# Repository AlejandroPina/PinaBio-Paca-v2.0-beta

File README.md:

# PinaBio Paca v2.0 beta

[English](README.en.md)

Placa experimental para registrar ECG, pulso óptico (PPG), respuesta galvánica de la piel (GSR), dos bandas de respiración y temperatura, y transmitir los datos por BLE. El uso previsto es investigación y biofeedback; no es un dispositivo médico.

La nueva placa **PINABio "Paca" v.2.0.** se encuentra en [hardware/PinaBio-Paca-v2.0](hardware/PinaBio-Paca-v2.0/README.md). Es un proyecto editable de **KiCad 9.0.9**, con esquemático, PCB de cuatro capas, BOM, Gerbers, taladros y posiciones. Mide **84,50 × 53,11 mm**. KiCad 9.0.9 informa **ERC 0, DRC 0, 0 conexiones pendientes y 0 diferencias entre esquemático y PCB**. Los archivos de fabricación son una salida de prototipo; falta la inspección independiente de huellas y la validación eléctrica de la primera placa ensamblada.

## Qué lleva

- ESP32-S3-MINI-1U-N8 con antena externa U.FL, BLE y Wi-Fi desactivado.
- Dos ADS122C04: uno dedicado al ECG a 600 SPS y otro para GSR, respiración torácica, respiración abdominal y AUX.
- MCP6004, módulo AD8232 externo, módulo GY-MAX30102 externo y módulo CJMCU-30205 externo.
- LiPo protegida de una celda, BQ24074 con power-path, TPS63070 para 3V3_SYS y TLV75530PDBVR a 3,0 V solo para la temperatura.
- Un USB-C soldado en el borde para carga, programación y datos. El interruptor exterior DPDT ON-ON controla el modo del BQ24074 y la habilitación del TPS63070. Con ON y USB, el sistema funciona desde la batería y no carga.
- No hay cortes automáticos en los sensores ni aislamiento USB en la placa. Para adquirir con una persona conectada y USB presente se requiere un aislador USB externo apto para ese uso.

## Documentación

- [Proyecto y conexiones de la PCB](hardware/PinaBio-Paca-v2.0/README.md)
- [Especificación de hardware](docs/es/especificacion.md)
- [Alimentación y USB](docs/es/alimentacion-usb.md)
- [Protocolo y datos](docs/es/protocolo.md)
- [Comparación con V1](docs/es/comparacion-v1.md)

**Antes de encargar montaje:** confirmar orientación y dimensiones del USB-C, TPS63070, todos los conectores y el interruptor cableado; medir los tres módulos externos reales; verificar las transiciones ON/OFF/USB y las tensiones del cargador y reguladores. Los informes de KiCad no sustituyen estas pruebas.

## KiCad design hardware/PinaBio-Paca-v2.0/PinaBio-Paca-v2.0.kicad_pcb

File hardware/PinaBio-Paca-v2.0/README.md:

# PINABio "Paca" v.2.0.

[English](README.en.md) · [Especificación completa](../../docs/es/especificacion.md) · [Alimentación y USB](../../docs/es/alimentacion-usb.md)

Proyecto editable de **KiCad 9.0.9**, cuatro capas, **84,50 × 53,11 mm**. Implementa la arquitectura cerrada del proyecto: un USB-C soldado, BQ24074 en standby mediante interruptor exterior, sin MOSFET de corte de VBUS, dos reguladores, sin cortes automáticos de sensores ni pull-ups nuevos de I²C, dos masas unidas solo en NT1 y keepout de cobre en todas las capas bajo el extremo U.FL del ESP32. La zona del TPS63070 y la bobina mantiene los nodos SW_L1 y SW_L2 en F.Cu, 0,40 mm y sin vías; la huella RNM conserva el pin 1 arriba a la izquierda y la numeración antihoraria.

## Archivos y verificación

- `PinaBio-Paca-v2.0.kicad_sch`, `.kicad_pcb` y `.kicad_pro`: esquemático y PCB.
- `PinaBio.kicad_sym`, `lib.pretty/`, `sym-lib-table` y `fp-lib-table`: bibliotecas necesarias.
- `bom.csv`: lista de materiales con MPN. L1 es **Coilcraft XAL4020-152MEC**.
- `fab/`: Gerbers de las cuatro capas, máscaras, pasta, serigrafía, contorno, taladros PTH/NPTH y `position.csv` en milímetros. `PinaBio-Paca-v2.0-Gerbers.zip` agrupa los 14 archivos de placa y taladro para subirlos al fabricante; BOM y posiciones se entregan por separado.
- `final-erc.txt` y `final-parity.txt`: **ERC 0, DRC 0, 0 sin conectar y paridad esquema-PCB 0**, ejecutados con KiCad 9.0.9.
- `Logo PINA-reducido.jfif`: imagen fuente del logo que se convirtió a serigrafía monocroma.

Los Gerbers son **de prototipo**. Antes de fabricar o montar, otra persona debe cotejar las huellas con los componentes comprados y ensayar una primera unidad, en especial la orientación del USB-C y TPS63070, las transiciones ON/OFF/USB y el cableado de los módulos externos.

## Conectores

| Referencia | Conexión por orden de pin |
|---|---|
| J1 | USB-C HCTL HC-TYPE-C-16P-01A, boca en el borde inferior; D+ y D− pasan por USBLC6-2SC6 y resistencias de 22 Ω. |
| J2 BATT | 1 BAT+ protegido, 2 GND, 3 TS/NTC. JST PH de 3 pines. La serigrafía usa «BATT» debajo del conector. |
| J3 ECG | 1 AGND, 2 3V3_A, 3 ECG_OUT, 4 LO_N, 5 LO_P, 6 3V3_A (SDN permanentemente habilitado). Orden del módulo rojo: GND, 3.3V, OUTPUT, LO−, LO+, SDN. |
| J4 PPG | 1 3V3_SYS/VIN, 2 GND, 3 SCL, 4 SDA, 5 INT. «VIN» identifica la alimentación del módulo; las otras cuatro señales están rotuladas junto a sus pines. |
| J5 TEMP | 1 3V0_TEMP, 2 GND, 3 SDA, 4 SCL. JST PH de 4 pines; unir A0/A1/A2 a GND en el módulo CJMCU-30205. |
| J6 GSR | 1 señal GSR, 2 AGND. |
| J7 RESP T | 1 señal torácica, 2 AGND. |
| J8 RESP A | 1 señal abdominal, 2 AGND. |
| J9 BATT METER | 1 BAT+ conmutado por Q4 BSS84/Q5 BSS138, 2 GND. JST PH B2B-PH-K-S(LF)(SN), reservado para el medidor de batería. |

J9 solo entrega tensión cuando está activo **3V3_SYS** (ON con batería u OFF con USB). Q4 tiene una resistencia de 1 MΩ entre puerta y fuente. La alimentación del medidor procede de BAT_PROT y no está destinada a alimentar otros módulos.

## Interruptor y alimentación

SW1 son **seis taladros para cable**, no una huella para soldar el interruptor. La pieza de referencia en la caja es C&K **7201SYZQE**, DPDT ON-ON. Puede emplearse otro DPDT ON-ON de seis terminales, como un MTS-202, después de verificar con multímetro sus comunes y contactos. Taladros 1–6 corresponden a terminales 1–6 de la referencia C&K: 1 VLOG, 2 EN2_CE, 3 GND, 4 BAT_PROT, 5 TPS_EN y 6 VLOG.

R39 de **10 kΩ, 1 %**, junto al pin EN del TPS63070, separa TPS_EN de TPS_EN_IC. R12 de 100 kΩ queda al lado del interruptor. PS/SYNC va a masa para PWM forzado. El TLV75530PDBVR alimenta **solo** el módulo de temperatura a 3,0 V; R3 de VBUS continúa en **0 Ω**.

Con OFF y USB se carga la batería y la placa puede programarse. Con ON y USB el BQ24074 está en standby: el sistema se alimenta de la LiPo, USB lleva datos y la batería no carga. Para conectar a una persona en ese modo se exige un aislador USB externo apropiado. No hay aislador ni desconexión automática de sensores en la PCB.

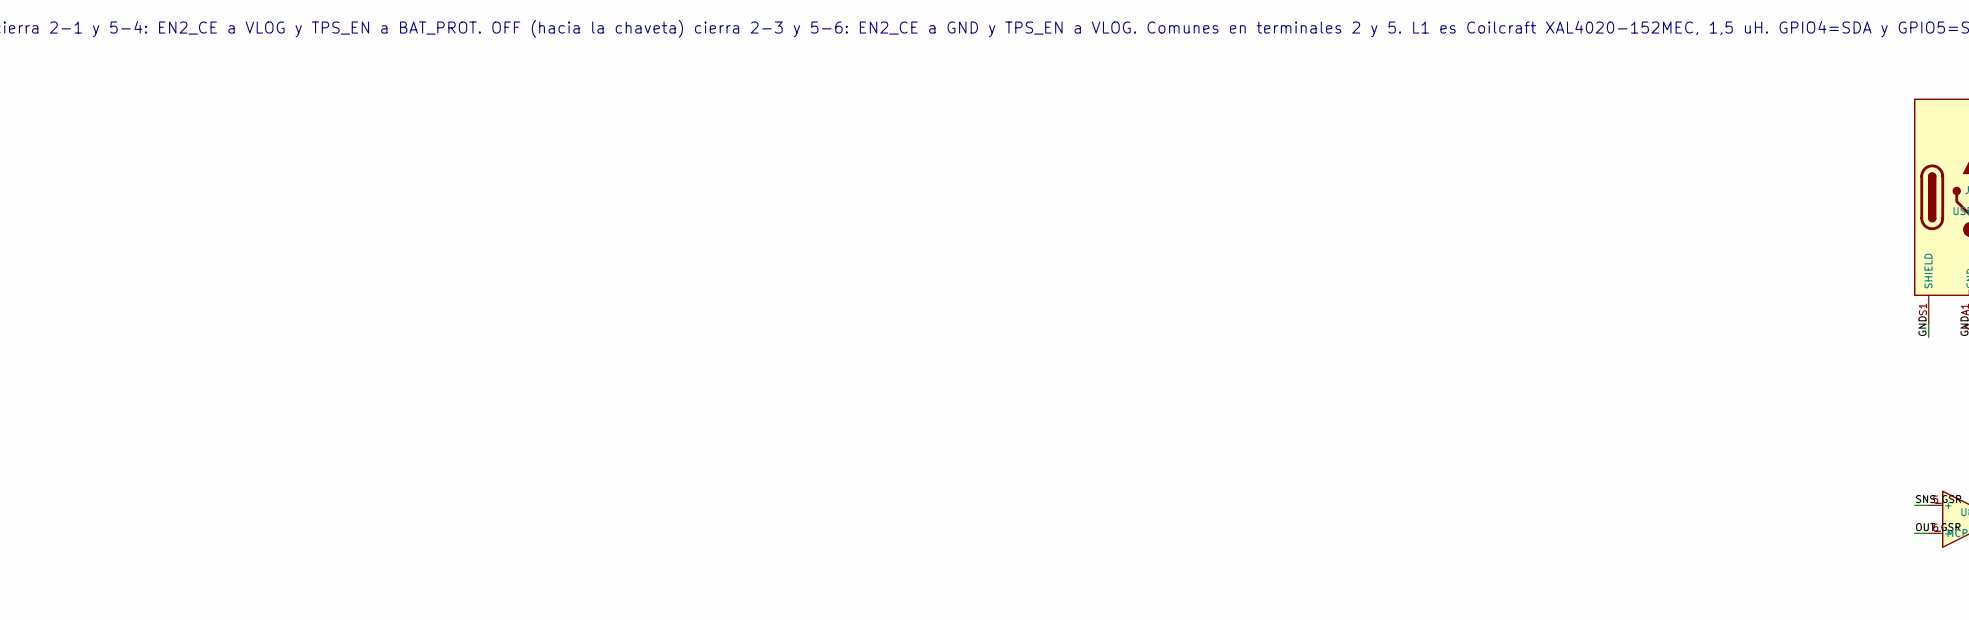
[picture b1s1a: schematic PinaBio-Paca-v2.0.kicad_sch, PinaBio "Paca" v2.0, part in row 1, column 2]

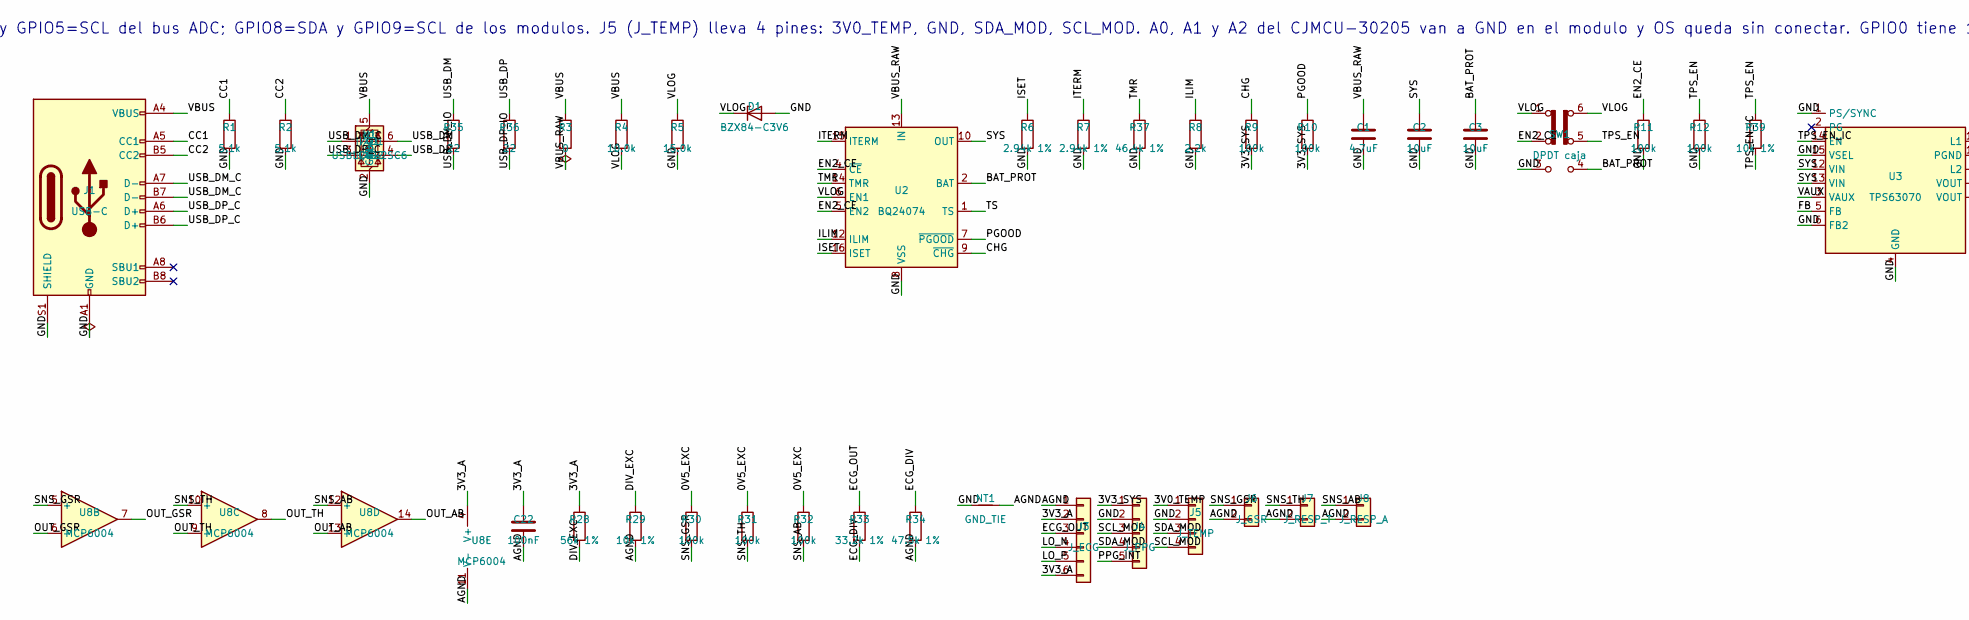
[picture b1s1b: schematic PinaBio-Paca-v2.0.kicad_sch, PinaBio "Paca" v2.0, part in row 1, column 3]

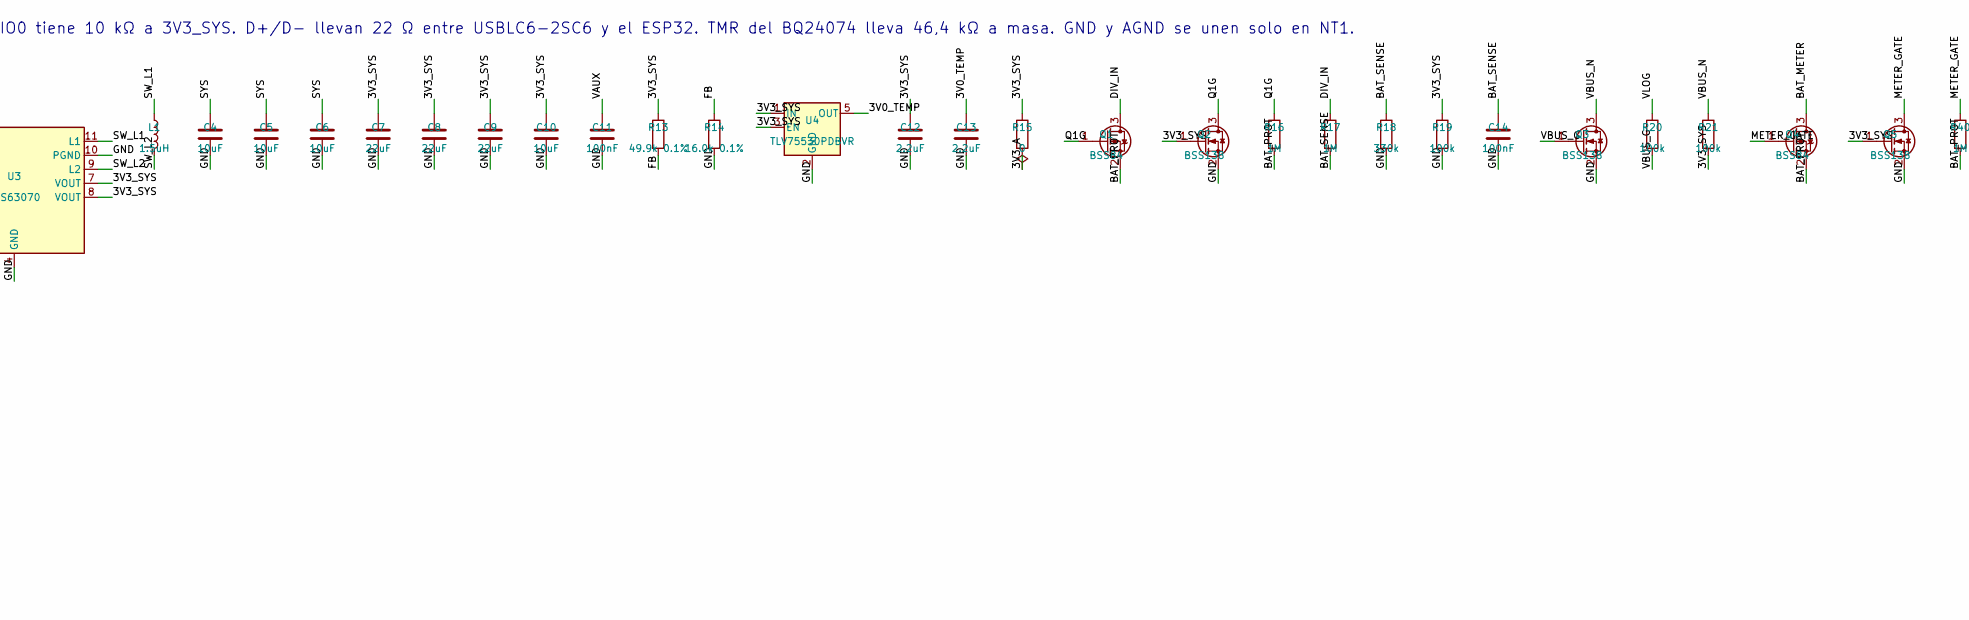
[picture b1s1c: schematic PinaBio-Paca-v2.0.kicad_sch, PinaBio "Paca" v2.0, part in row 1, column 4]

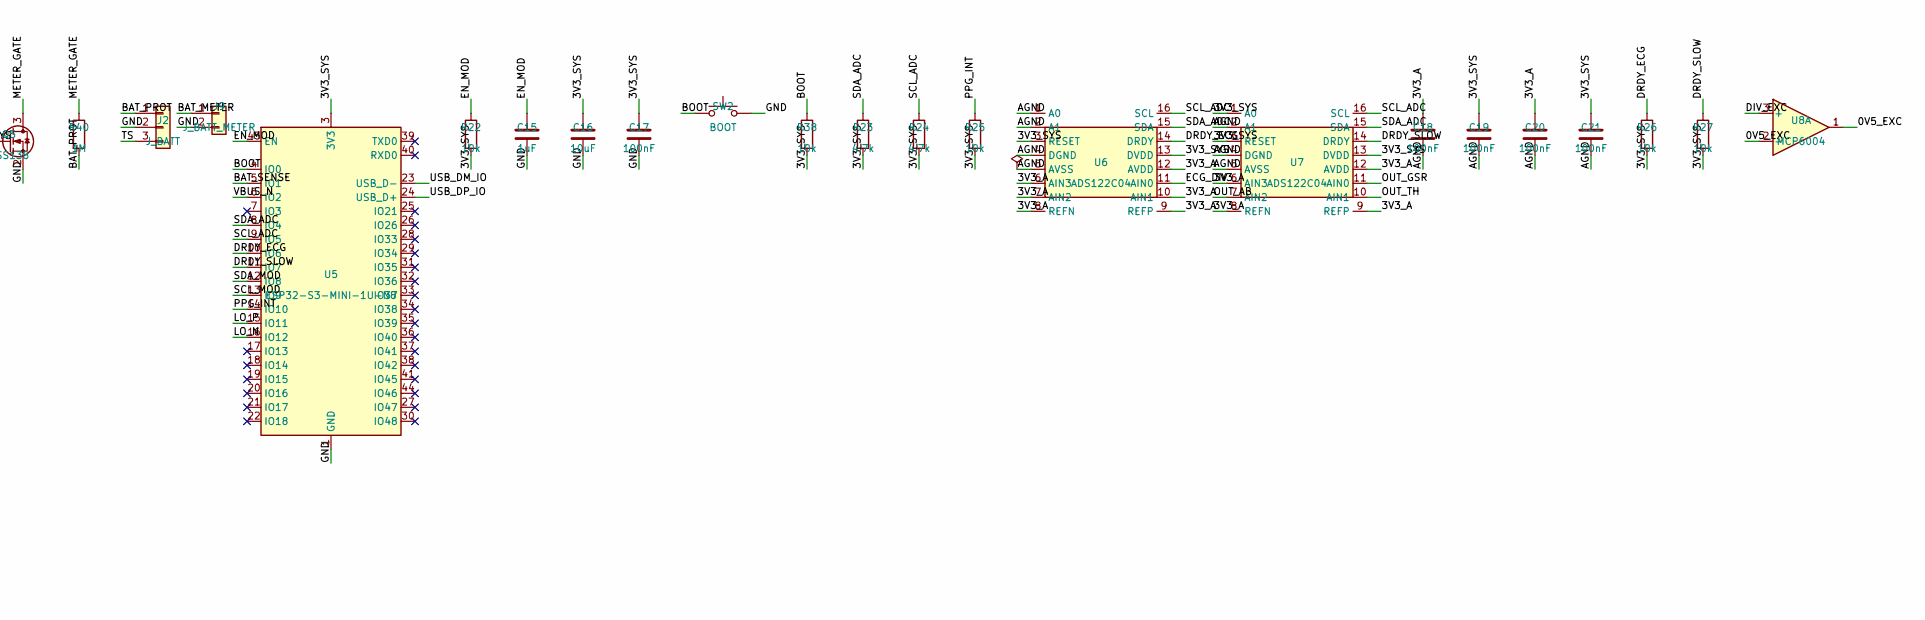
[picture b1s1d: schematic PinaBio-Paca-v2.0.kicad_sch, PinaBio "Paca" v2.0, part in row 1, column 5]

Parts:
C1: 4.7uF; C_0603_1608Metric; Voltage 16V; MPN CL10A475KO8NNNC
C2, C3, C4, C5, C6, C10, C16: 10uF; C_0805_2012Metric; Voltage 16V; MPN CL21A106KOQNNNE
C7, C8, C9: 22uF; C_0805_2012Metric; Voltage 25V; MPN CL21A226MAYNNNE
C11, C14, C17, C18, C19, C20, C21, C22: 100nF; C_0603_1608Metric; Voltage 50V; MPN CL10B104KB8NNNC
C12, C13: 2.2uF; C_0805_2012Metric; Voltage 25V; MPN CL21B225KAFNNNE
C15: 1uF; C_0603_1608Metric; Voltage 50V; MPN CL10A105KB8NNNC
D1: BZX84-C3V6; SOT-23; MPN BZX84-C3V6,215
J1: USB-C; USB_C_Receptacle_HCTL_HC-TYPE-C-16P-01A; MPN HC-TYPE-C-16P-01A
J2: J_BATT; JST_PH_B3B-PH-K_1x03_P2.00mm_Vertical; MPN B3B-PH-K-S(LF)(SN)
J3: J_ECG; JST_PH_B6B-PH-K_1x06_P2.00mm_Vertical; MPN B6B-PH-K-S(LF)(SN)
J4: J_PPG; JST_PH_B5B-PH-K_1x05_P2.00mm_Vertical; MPN B5B-PH-K-S(LF)(SN)
J5: J_TEMP; JST_PH_B4B-PH-K_1x04_P2.00mm_Vertical; MPN B4B-PH-K-S(LF)(SN)
J6: J_GSR; JST_PH_B2B-PH-K_1x02_P2.00mm_Vertical; MPN B2B-PH-K-S(LF)(SN)
J7: J_RESP_T; JST_PH_B2B-PH-K_1x02_P2.00mm_Vertical; MPN B2B-PH-K-S(LF)(SN)
J8: J_RESP_A; JST_PH_B2B-PH-K_1x02_P2.00mm_Vertical; MPN B2B-PH-K-S(LF)(SN)
J9: J_BATT_METER; JST_PH_B2B-PH-K_1x02_P2.00mm_Vertical; MPN B2B-PH-K-S(LF)(SN)
L1: 1.5uH; L_Coilcraft_XAL4020-XXX; MPN XAL4020-152MEC
NT1: GND_TIE; GndTie_2mm
Q1, Q4: BSS84; SOT-23; MPN BSS84LT1G
Q2, Q3, Q5: BSS138; SOT-23; MPN BSS138LT1G
R1, R2: 5.1k; R_0603_1608Metric; MPN RC0603FR-075K1L
R3, R15: 0; R_0603_1608Metric; MPN RC0603JR-070RL
R4: 10.0k; R_0603_1608Metric; MPN RC0603FR-0710KL
R5: 15.0k; R_0603_1608Metric; MPN RC0603FR-0715KL
R6, R7: 2.94k 1%; R_0603_1608Metric; MPN RC0603FR-072K94L
R8: 2.2k; R_0603_1608Metric; MPN RC0603FR-072K2L
R9, R10, R11, R12, R19, R20, R21, R30, R31, R32: 100k; R_0603_1608Metric; MPN RC0603FR-07100KL
R13: 49.9k 0.1%; R_0603_1608Metric; MPN RT0603BRD0749K9L
R14: 16.0k 0.1%; R_0603_1608Metric; MPN RT0603BRD0716KL
R16, R17, R40: 1M; R_0603_1608Metric; MPN RC0603FR-071ML
R18: 330k; R_0603_1608Metric; MPN RC0603FR-07330KL
R22, R25, R26, R27, R38: 10k; R_0603_1608Metric; MPN RC0603FR-0710KL
R23, R24: 4.7k; R_0603_1608Metric; MPN RC0603FR-074K7L
R28: 56k 1%; R_0603_1608Metric; MPN RC0603FR-0756KL
R29, R39: 10k 1%; R_0603_1608Metric; MPN RC0603FR-0710KL
R33: 33.2k 1%; R_0603_1608Metric; MPN RC0603FR-0733K2L
R34: 47.5k 1%; R_0603_1608Metric; MPN RC0603FR-0747K5L
R35, R36: 22; R_0603_1608Metric; MPN RC0603FR-0722RL
R37: 46.4k 1%; R_0603_1608Metric; MPN RC0603FR-0746K4L
SW1: DPDT caja; SW_ext_6pad
SW2: BOOT; SW_SPST_B3U-1000P; MPN B3U-1000P
U1: USBLC6-2SC6; SOT-23-6; MPN USBLC6-2SC6
U2: BQ24074; VQFN-16-1EP_3x3mm_P0.5mm_EP1.6x1.6mm; MPN BQ24074RGTR
U3: TPS63070; TPS63070RNM; MPN TPS63070RNMR
U4: TLV75530PDBVR; SOT-23-5; MPN TLV75530PDBVR
U5: ESP32-S3-MINI-1U-N8; ESP32-S2-MINI-1U; MPN ESP32-S3-MINI-1U-N8
U6, U7: ADS122C04; TSSOP-16_4.4x5mm_P0.65mm; MPN ADS122C04IPWR
U8: MCP6004; SOIC-14_3.9x8.7mm_P1.27mm; MPN MCP6004-I/SL

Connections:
/0V5_EXC: R30.1, R31.1, R32.1, U8.1, U8.2 (-)
/3V0_TEMP: C13.1, J5.1, U4.5 (OUT)
/3V3_A: C18.1, C20.1, C22.1, J3.2, J3.6, R15.2, R28.1, U6.6 (AIN3), U6.7 (AIN2), U6.8 (REFN), U6.9 (REFP), U6.10 (AIN1), U6.12 (AVDD), U7.6 (AIN3), U7.8 (REFN), U7.9 (REFP), U7.12 (AVDD), U8.4 (V+)
/3V3_SYS: C7.1, C8.1, C9.1, C10.1, C12.1, C16.1, C17.1, C19.1, C21.1, J4.1, Q2.1 (G), Q5.1 (G), R9.2, R10.2, R13.1, R15.1, R19.1, R21.2, R22.2, R23.2, R24.2, R25.2, R26.2, R27.2, R38.2, U3.7 (VOUT), U3.8 (VOUT), U4.1 (IN), U4.3 (EN), U5.3 (3V3), U6.3 (RESET), U6.13 (DVDD), U7.1 (A0), U7.3 (RESET), U7.13 (DVDD)
/AGND: C18.2, C19.2, C20.2, C21.2, C22.2, J3.1, J6.2, J7.2, J8.2, NT1.2, R29.2, R34.2, U6.1 (A0), U6.2 (A1), U6.4 (DGND), U6.5 (AVSS), U7.2 (A1), U7.4 (DGND), U7.5 (AVSS), U8.11 (V-)
/BAT_METER: J9.1, Q4.3 (D)
/BAT_PROT: C3.1, J2.1, Q1.2 (S), Q4.2 (S), R16.2, R40.2, SW1.4 (A), U2.2 (BAT), U2.3 (BAT)
/BAT_SENSE: C14.1, R17.2, R18.1, U5.5 (IO1)
/BOOT: R38.1, SW2.1, U5.4 (IO0)
/CC1: J1.A5 (CC1), R1.1
/CC2: J1.B5 (CC2), R2.1
/CHG: R9.1, U2.9 (~CHG)
/DIV_EXC: R28.2, R29.1, U8.3 (+)
/DIV_IN: Q1.3 (D), R17.1
/DRDY_ECG: R26.1, U5.10 (IO6), U6.14 (DRDY)
/DRDY_SLOW: R27.1, U5.11 (IO7), U7.14 (DRDY)
/ECG_DIV: R33.2, R34.1, U6.11 (AIN0)
/ECG_OUT: J3.3, R33.1
/EN2_CE: R11.1, SW1.2 (B), U2.4 (~CE), U2.5 (EN2)
/EN_MOD: C15.1, R22.1, U5.45 (EN)
/FB: R13.2, R14.1, U3.5 (FB)
/GND: C1.2, C2.2, C3.2, C4.2, C5.2, C6.2, C7.2, C8.2, C9.2, C10.2, C11.2, C12.2, C13.2, C14.2, C15.2, C16.2, C17.2, D1.1 (A), J1.A1 (GND), J1.A12 (GND), J1.B1 (GND), J1.B12 (GND), J1.S1 (SHIELD), J2.2, J4.2, J5.2, J9.2, NT1.1, Q2.2 (S), Q3.2 (S), Q5.2 (S), R1.2, R2.2, R5.2, R6.2, R7.2, R8.2, R11.2, R12.2, R14.2, R18.2, R19.2, R37.2, SW1.3 (C), SW2.2, U1.2 (GND), U2.8 (VSS), U2.17 (VSS), U3.1 (PS/SYNC), U3.4 (GND), U3.6 (FB2), U3.10 (PGND), U3.15 (VSEL), U4.2 (GND), U5.1 (GND), U5.2 (GND), U5.42 (GND), U5.43 (GND), U5.46 (GND), U5.47 (GND), U5.48 (GND), U5.49 (GND), U5.50 (GND), U5.51 (GND), U5.52 (GND), U5.53 (GND), U5.54 (GND), U5.55 (GND), U5.56 (GND), U5.57 (GND), U5.58 (GND), U5.59 (GND), U5.60 (GND), U5.61 (GND), U5.62 (GND), U5.63 (GND), U5.64 (GND), U5.65 (GND)
/ILIM: R8.1, U2.12 (ILIM)
/ISET: R6.1, U2.16 (ISET)
/ITERM: R7.1, U2.15 (ITERM)
/LO_N: J3.4, U5.16 (IO12)
/LO_P: J3.5, U5.15 (IO11)
/METER_GATE: Q4.1 (G), Q5.3 (D), R40.1
/OUT_AB: U7.7 (AIN2), U8.13 (-), U8.14
/OUT_GSR: U7.11 (AIN0), U8.6 (-), U8.7
/OUT_TH: U7.10 (AIN1), U8.8, U8.9 (-)
/PGOOD: R10.1, U2.7 (~PGOOD)
/PPG_INT: J4.5, R25.1, U5.14 (IO10)
/Q1G: Q1.1 (G), Q2.3 (D), R16.1
/SCL_ADC: R24.1, U5.9 (IO5), U6.16 (SCL), U7.16 (SCL)
/SCL_MOD: J4.3, J5.4, U5.13 (IO9)
/SDA_ADC: R23.1, U5.8 (IO4), U6.15 (SDA), U7.15 (SDA)
/SDA_MOD: J4.4, J5.3, U5.12 (IO8)
/SNS_AB: J8.1, R32.2, U8.12 (+)
/SNS_GSR: J6.1, R30.2, U8.5 (+)
/SNS_TH: J7.1, R31.2, U8.10 (+)
/SW_L1: L1.1, U3.11 (L1)
/SW_L2: L1.2, U3.9 (L2)
/SYS: C2.1, C4.1, C5.1, C6.1, U2.10 (OUT), U2.11 (OUT), U3.12 (VIN), U3.13 (VIN)
/TMR: R37.1, U2.14 (TMR)
/TPS_EN: R12.1, R39.1, SW1.5 (B)
/TPS_EN_IC: R39.2, U3.14 (EN)
/TS: J2.3, U2.1 (TS)
/USB_DM: R35.1, U1.6 (I/O1)
/USB_DM_C: J1.A7 (D-), J1.B7 (D-), U1.1 (I/O1)
/USB_DM_IO: R35.2, U5.23 (USB_D-)
/USB_DP: R36.1, U1.4 (I/O2)
/USB_DP_C: J1.A6 (D+), J1.B6 (D+), U1.3 (I/O2)
/USB_DP_IO: R36.2, U5.24 (USB_D+)
/VAUX: C11.1, U3.3 (VAUX)
/VBUS: J1.A4 (VBUS), J1.A9 (VBUS), J1.B4 (VBUS), J1.B9 (VBUS), R3.1, R4.1, U1.5 (VBUS)
/VBUS_G: Q3.1 (G), R20.2
/VBUS_N: Q3.3 (D), R21.1, U5.6 (IO2)
/VBUS_RAW: C1.1, R3.2, U2.13 (IN)
/VLOG: D1.3 (K), R4.2, R5.1, R20.1, SW1.1 (A), SW1.6 (C), U2.6 (EN1)

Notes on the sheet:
PinaBio "Paca" v2.0. SPEC-0.9. Sensores sin corte en serie. Interruptor de caja C&K 7201SYZQE, DPDT ON-ON, cable 1:1. ON (lejos de la chaveta) cierra 2-1 y 5-4: EN2_CE a VLOG y TPS_EN a BAT_PROT. OFF (hacia la chaveta) cierra 2-3 y 5-6: EN2_CE a GND y TPS_EN a VLOG. Comunes en terminales 2 y 5. L1 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

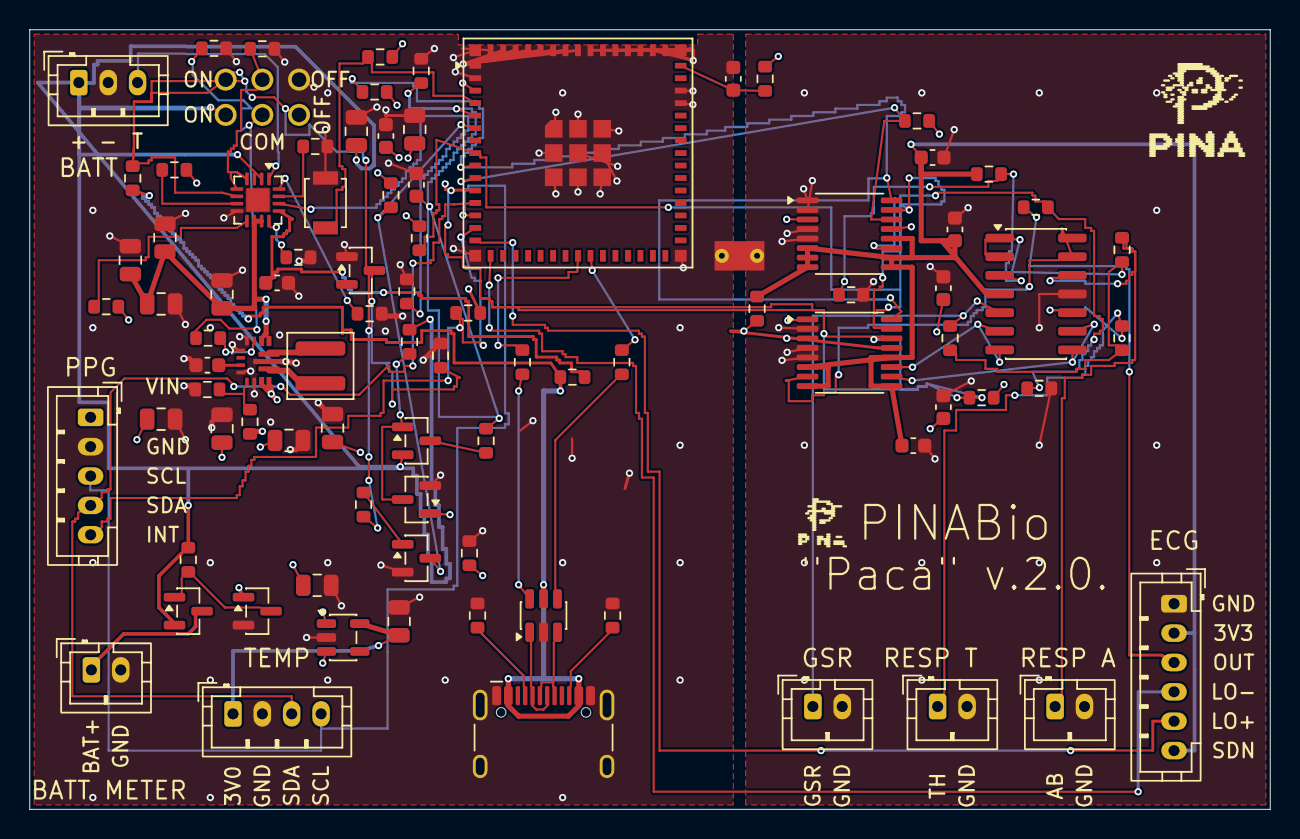
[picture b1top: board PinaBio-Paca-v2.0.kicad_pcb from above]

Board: 4 copper layers, 84.5 x 53.1 mm, 89 parts (0 on the bottom side), 60 nets.

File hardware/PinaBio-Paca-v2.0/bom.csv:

Reference,Value,Footprint,Manufacturer,MPN,Voltage,Dielectric,Datasheet,Qty
"J1","USB-C","Connector_USB:USB_C_Receptacle_HCTL_HC-TYPE-C-16P-01A","HCTL","HC-TYPE-C-16P-01A","","","~",1
"R1 R2","5.1k","Resistor_SMD:R_0603_1608Metric","YAGEO","RC0603FR-075K1L","","","~",2
"U1","USBLC6-2SC6","Package_TO_SOT_SMD:SOT-23-6","STMicroelectronics","USBLC6-2SC6","","","https://www.st.com/resource/en/datasheet/usblc6-2.pdf",1
"R35 R36","22","Resistor_SMD:R_0603_1608Metric","YAGEO","RC0603FR-0722RL","","","~",2
"R3 R15","0","Resistor_SMD:R_0603_1608Metric","YAGEO","RC0603JR-070RL","","","~",2
"R4","10.0k","Resistor_SMD:R_0603_1608Metric","YAGEO","RC0603FR-0710KL","","","~",1
"R5","15.0k","Resistor_SMD:R_0603_1608Metric","YAGEO","RC0603FR-0715KL","","","~",1
"D1","BZX84-C3V6","Package_TO_SOT_SMD:SOT-23","Nexperia","BZX84-C3V6,215","","","https://assets.nexperia.com/documents/data-sheet/BZX84_SERIES.pdf",1
"U2","BQ24074","Package_DFN_QFN:VQFN-16-1EP_3x3mm_P0.5mm_EP1.6x1.6mm","Texas Instruments","BQ24074RGTR","","","https://www.ti.com/lit/ds/symlink/bq24074.pdf",1
"R6 R7","2.94k 1%","Resistor_SMD:R_0603_1608Metric","YAGEO","RC0603FR-072K94L","","","https://www.ti.com/lit/ds/symlink/bq24074.pdf",2
"R37","46.4k 1%","Resistor_SMD:R_0603_1608Metric","YAGEO","RC0603FR-0746K4L","","","https://www.ti.com/lit/ds/symlink/bq24074.pdf",1
"R8","2.2k","Resistor_SMD:R_0603_1608Metric","YAGEO","RC0603FR-072K2L","","","~",1
"R9 R10 R11 R12 R19 R20 R21 R30 R31 R32","100k","Resistor_SMD:R_0603_1608Metric","YAGEO","RC0603FR-07100KL","","","~",10
"C1","4.7uF","Capacitor_SMD:C_0603_1608Metric","Samsung Electro-Mechanics","CL10A475KO8NNNC","16V","X5R","~",1
"C2 C3 C4 C5 C6 C10 C16","10uF","Capacitor_SMD:C_0805_2012Metric","Samsung Electro-Mechanics","CL21A106KOQNNNE","16V","X5R","~",7
"SW1","DPDT caja","PinaBio:SW_ext_6pad","","","","","https://media.digikey.com/pdf/Data%20Sheets/C&K/7000%20Mini%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",1
"R39 R29","10k 1%","Resistor_SMD:R_0603_1608Metric","YAGEO","RC0603FR-0710KL","","","https://www.ti.com/lit/ds/symlink/tps63070.pdf",2
"U3","TPS63070","PinaBio:TPS63070RNM","Texas Instruments","TPS63070RNMR","","","https://www.ti.com/lit/ds/symlink/tps63070.pdf",1
"L1","1.5uH","Inductor_SMD:L_Coilcraft_XAL4020-XXX","Coilcraft","XAL4020-152MEC","","","https://www.coilcraft.com/getmedia/6adcb47d-8b55-416c-976e-1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",1
"C7 C8 C9","22uF","Capacitor_SMD:C_0805_2012Metric","Samsung Electro-Mechanics","CL21A226MAYNNNE","25V","X5R","~",3
"C11 C14 C17 C18 C19 C20 C21 C22","100nF","Capacitor_SMD:C_0603_1608Metric","Samsung Electro-Mechanics","CL10B104KB8NNNC","50V","X7R","~",8
"R13","49.9k 0.1%","Resistor_SMD:R_0603_1608Metric","YAGEO","RT0603BRD0749K9L","","","https://www.ti.com/lit/ds/symlink/tps63070.pdf",1
"R14","16.0k 0.1%","Resistor_SMD:R_0603_1608Metric","YAGEO","RT0603BRD0716KL","","","https://www.ti.com/lit/ds/symlink/tps63070.pdf",1
"U4","TLV75530PDBVR","Package_TO_SOT_SMD:SOT-23-5","Texas Instruments","TLV75530PDBVR","","","https://www.ti.com/lit/ds/symlink/tlv755p.pdf",1
"C12 C13","2.2uF","Capacitor_SMD:C_0805_2012Metric","Samsung Electro-Mechanics","CL21B225KAFNNNE","25V","X7R","~",2
"Q1 Q4","BSS84","Package_TO_SOT_SMD:SOT-23","onsemi","BSS84LT1G","","","https://www.onsemi.com/pdf/datasheet/bss84-d.pdf",2
"Q2 Q3 Q5","BSS138","Package_TO_SOT_SMD:SOT-23","onsemi","BSS138LT1G","","","https://www.onsemi.com/pdf/datasheet/bss138-d.pdf",3
"R16 R17 R40","1M","Resistor_SMD:R_0603_1608Metric","YAGEO","RC0603FR-071ML","","","~",3
"R18","330k","Resistor_SMD:R_0603_1608Metric","YAGEO","RC0603FR-07330KL","","","~",1
"J2","J_BATT","Connector_JST:JST_PH_B3B-PH-K_1x03_P2.00mm_Vertical","JST","B3B-PH-K-S(LF)(SN)","","","~",1
"J9","J_BATT_METER","Connector_JST:JST_PH_B2B-PH-K_1x02_P2.00mm_Vertical","JST","B2B-PH-K-S(LF)(SN)","","","~",1
"U5","ESP32-S3-MINI-1U-N8","RF_Module:ESP32-S2-MINI-1U","Espressif","ESP32-S3-MINI-1U-N8","","","https://www.espressif.com/sites/default/files/documentation/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",1
"R22 R38 R25 R26 R27","10k","Resistor_SMD:R_0603_1608Metric","YAGEO","RC0603FR-0710KL","","","https://www.espressif.com/sites/default/files/documentation/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",5
"C15","1uF","Capacitor_SMD:C_0603_1608Metric","Samsung Electro-Mechanics","CL10A105KB8NNNC","50V","X5R","~",1
"SW2","BOOT","Button_Switch_SMD:SW_SPST_B3U-1000P","Omron","B3U-1000P","","","~",1
"R23 R24","4.7k","Resistor_SMD:R_0603_1608Metric","YAGEO","RC0603FR-074K7L","","","~",2
"U6 U7","ADS122C04","Package_SO:TSSOP-16_4.4x5mm_P0.65mm","Texas Instruments","ADS122C04IPWR","","","https://www.ti.com/lit/ds/symlink/ads122c04.pdf",2
"U8","MCP6004","Package_SO:SOIC-14_3.9x8.7mm_P1.27mm","Microchip","MCP6004-I/SL","","","https://ww1.microchip.com/downloads/en/DeviceDoc/MCP6001-1R-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",1
"R28","56k 1%","Resistor_SMD:R_0603_1608Metric","YAGEO","RC0603FR-0756KL","","","~",1
"R33","33.2k 1%","Resistor_SMD:R_0603_1608Metric","YAGEO","RC0603FR-0733K2L","","","~",1
"R34","47.5k 1%","Resistor_SMD:R_0603_1608Metric","YAGEO","RC0603FR-0747K5L","","","~",1
"J3","J_ECG","Connector_JST:JST_PH_B6B-PH-K_1x06_P2.00mm_Vertical","JST","B6B-PH-K-S(LF)(SN)","","","~",1
"J4","J_PPG","Connector_JST:JST_PH_B5B-PH-K_1x05_P2.00mm_Vertical","JST","B5B-PH-K-S(LF)(SN)","","","~",1
"J5","J_TEMP","Connector_JST:JST_PH_B4B-PH-K_1x04_P2.00mm_Vertical","JST","B4B-PH-K-S(LF)(SN)","","","~",1
"J6","J_GSR","Connector_JST:JST_PH_B2B-PH-K_1x02_P2.00mm_Vertical","JST","B2B-PH-K-S(LF)(SN)","","","~",1
"J7","J_RESP_T","Connector_JST:JST_PH_B2B-PH-K_1x02_P2.00mm_Vertical","JST","B2B-PH-K-S(LF)(SN)","","","~",1
"J8","J_RESP_A","Connector_JST:JST_PH_B2B-PH-K_1x02_P2.00mm_Vertical","JST","B2B-PH-K-S(LF)(SN)","","","~",1

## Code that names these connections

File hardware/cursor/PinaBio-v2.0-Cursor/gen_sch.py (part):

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        1,
        {"3": "VLOG", "1": "GND"},
    )
    # BQ24074. Pin 15 is ITERM. Pin 14 is TMR: 46.4 kΩ 1% to ground.
    place(
        "BQ",
        "U2",
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        "PinaBio v.2.0. Cursor. SPEC-0.9. Sensores sin corte en serie. "
        "Interruptor de caja C&K 7201SYZQE, DPDT ON-ON, cable 1:1. ""ON (lejos de la chaveta) cierra 2-1 y 5-4: EN2_CE a VLOG y TPS_EN a BAT_PROT. ""OFF (hacia la chaveta) cierra 2-3 y 5-6: EN2_CE a GND y TPS_EN a VLOG. ""Comunes en terminales 2 y 5. L1 es Coilcraft XAL4020-152ME, 1,5 uH. "
        "GPIO4=SDA y GPIO5=SCL del bus ADC; GPIO8=SDA y GPIO9=SCL de los modulos. "
        "J5 (J_TEMP) lleva 4 pines: 3V0_TEMP, GND, SDA_MOD, SCL_MOD. A0, A1 y A2 del CJMCU-30205 van a GND en el modulo y OS queda sin conectar. "
        "GPIO0 tiene 10 kΩ a 3V3_SYS. D+/D− llevan 22 Ω entre USBLC6-2SC6 y el ESP32. "
        "TMR del BQ24074 lleva 46,4 kΩ a masa. GND y AGND se unen solo en NT1."
    )
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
